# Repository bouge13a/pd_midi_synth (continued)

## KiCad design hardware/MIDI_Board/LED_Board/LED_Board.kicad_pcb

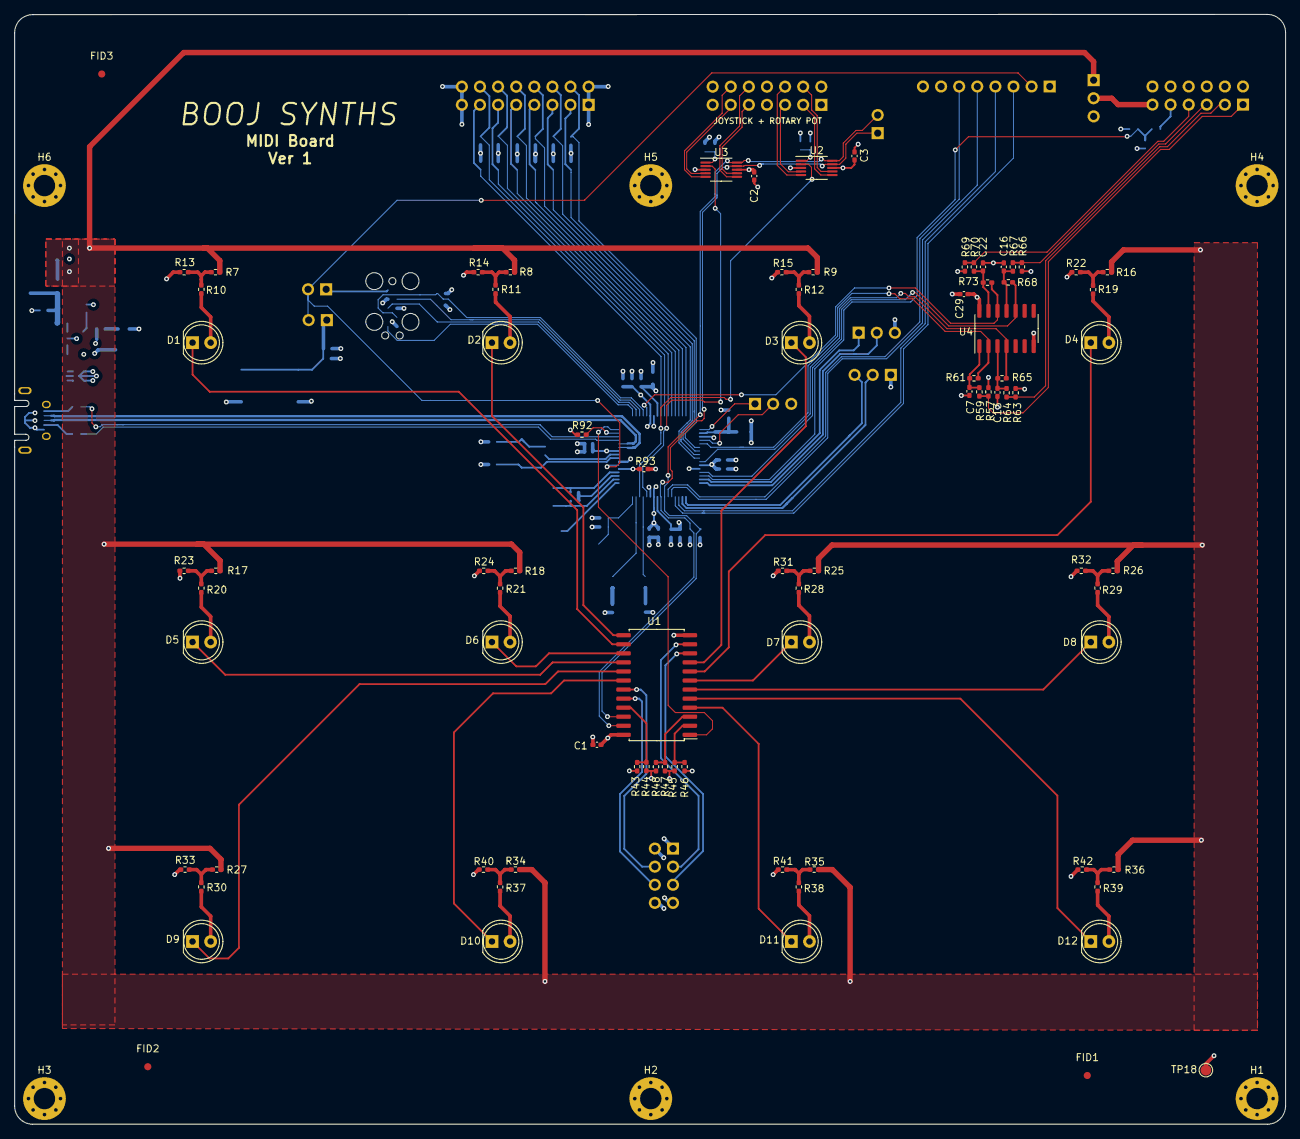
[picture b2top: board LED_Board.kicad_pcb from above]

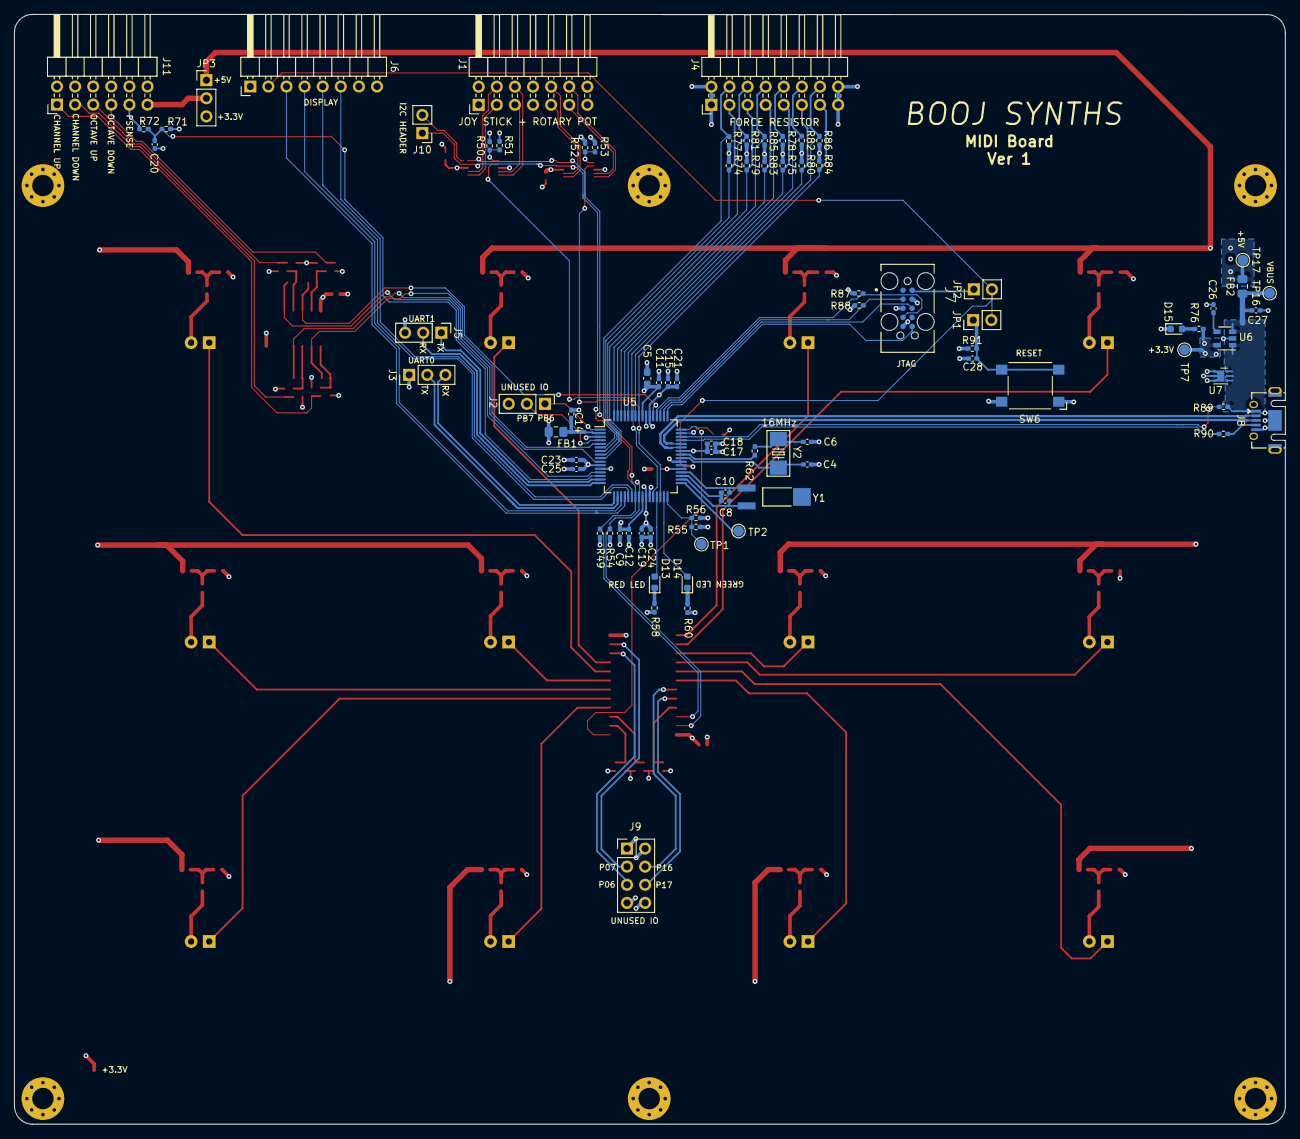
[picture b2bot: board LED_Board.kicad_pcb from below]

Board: 4 copper layers, 178.3 x 155.7 mm, 172 parts (82 on the bottom side), 129 nets.

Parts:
C1, C2, C3, C7, C11, C12, C13, C14, C16, C20, C21, C22, C23, C24, C25, C26, C28: 0.1uF; C_0402_1005Metric_Pad0.74x0.62mm_HandSolder
C4, C6: 10pF; C_0402_1005Metric_Pad0.74x0.62mm_HandSolder
C5: 2.2uF; C_0603_1608Metric_Pad1.08x0.95mm_HandSolder
C8, C10: 24pF; C_0402_1005Metric_Pad0.74x0.62mm_HandSolder
C9, C27: 1uF; C_0402_1005Metric_Pad0.74x0.62mm_HandSolder
C15, C17, C18, C19, C29: 0.01uF; C_0402_1005Metric_Pad0.74x0.62mm_HandSolder
D1, D2, D3, D4, D5, D6, D7, D8, D9, D10, D11, D12: LED; LED_D5.0mm
D13: LED_RED; LED_0603_1608Metric
D14: LED_GREEN; LED_0603_1608Metric
D15: +3.3V; LED_0603_1608Metric
FB1, FB2: 600_Ohm@100MHz; L_0805_2012Metric_Pad1.15x1.40mm_HandSolder
FID1, FID2, FID3: Fiducial_1mm_Mask3mm
H1, H2, H3, H4, H5, H6: MountingHole_Pad; MountingHole_3mm_Pad_Via
J1: Conn_02x07_Odd_Even; PinHeader_2x07_P2.54mm_Horizontal
J2, J3, J5: Conn_01x03_Male; PinHeader_1x03_P2.54mm_Vertical
J4: Conn_02x08_Odd_Even; PinHeader_2x08_P2.54mm_Horizontal
J6: Conn_01x08_Female; PinHeader_1x08_P2.54mm_Horizontal
J7: TC2050-IDC; TAG-CONNECT_TC2050-IDC
J8: USB_B_Micro; USB_Micro-AB_Molex_47590-0001
J9: Conn_02x04_Odd_Even; PinHeader_2x04_P2.54mm_Vertical
J10: Conn_01x02_Male; PinHeader_1x02_P2.54mm_Vertical
J11: Conn_02x06_Odd_Even; PinHeader_2x06_P2.54mm_Horizontal
JP1: Jumper_NC_Small; PinHeader_1x02_P2.54mm_Vertical
JP2: Jumper_NO_Small; PinHeader_1x02_P2.54mm_Vertical
JP3: Jumper_3_Open; PinHeader_1x03_P2.54mm_Vertical
R7, R8, R9, R13, R14, R15, R16, R17, R18, R22, R23, R24, R25, R26, R27, R31, R32, R33, R34, R35, R36, R40, R41, R42, R56, R61, R62, R65, R68, R73, R93: 0; R_0402_1005Metric_Pad0.72x0.64mm_HandSolder
R10, R11, R12, R19, R20, R21, R28, R29, R30, R37, R38, R39, R49, R54, R55, R57, R59, R63, R64, R66, R67, R69, R70, R71, R76, R87, R88, R91, R92: 10K; R_0402_1005Metric_Pad0.72x0.64mm_HandSolder
R43, R44, R45, R46, R47, R48, R50, R51, R52, R53, R58, R60: 4.7K; R_0402_1005Metric_Pad0.72x0.64mm_HandSolder
R72: 1K; R_0402_1005Metric_Pad0.72x0.64mm_HandSolder
R74, R75, R77, R78, R79, R80, R81, R82, R83, R84, R85, R86: 100K; R_0402_1005Metric_Pad0.72x0.64mm_HandSolder
R89, R90: 100; R_0402_1005Metric_Pad0.72x0.64mm_HandSolder
SW6: B3F-1000; SW_SPST_Omron_B3FS-100xP
TP1: WAKE_N; TestPoint_Pad_D1.5mm
TP2: HIB; TestPoint_Pad_D1.5mm
TP7: 3.3V; TestPoint_Pad_D1.5mm
TP16: VBUS; TestPoint_Pad_D1.5mm
TP17: +5V; TestPoint_Pad_D1.5mm
TP18: +3.3V; TestPoint_Pad_D1.5mm
U1: PCF8575PWR; SOIC-24W_7.5x15.4mm_P1.27mm
U2, U3: ADS1015IDGS; VSSOP-10_3x3mm_P0.5mm
U4: 74HC14; SOIC-14_3.9x8.7mm_P1.27mm
U5: TM4C123GH6PM; LQFP-64_10x10mm_P0.5mm
U6: TPS73633DBV; SOT-23-5
U7: TVS0500DRV; WSON-6-1EP_2x2mm_P0.65mm_EP1x1.6mm
Y1: 32.768KHz; XTAL_AB26TRB-32.768KHZ-T
Y2: 16MHz; CRYSTAL_5_3.2MM

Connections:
+3.3VA: C14.1, FB1.2, U5.2
+3V3: C1.1, C2.1, C3.1, C15.1, C17.1, C18.1, C19.1, C21.1, C23.1, C24.1, C25.1, C29.1, FB1.1, J1.1, J1.2, J4.1, J4.2, J4.15, J4.16, J6.7, JP3.3, R13.1, R14.1, R15.1, R22.1, R23.1, R24.1, R31.1, R32.1, R33.1, R40.1, R41.1, R42.1, R43.1, R45.1, R47.1, R49.1, R50.1, R52.1, R54.1, R55.1, R57.1, R63.1, R66.1, R69.1, R71.1, R76.1, R87.1, R88.1, R91.1, R93.2, TP7.1, TP18.1, U1.24, U2.8, U3.8, U4.14, U5.11, U5.26, U5.42, U5.54, U6.5
+5V: FB2.1, JP3.1, R7.1, R8.1, R9.1, R16.1, R17.1, R18.1, R25.1, R26.1, R27.1, R34.1, R35.1, R36.1, TP17.1
/MCU USB POWER IO/GNDX: C8.2, C10.1, U5.35
/MCU USB POWER IO/GREEN_LED: D14.2, U5.31
/MCU USB POWER IO/OSC0: C4.1, U5.40, Y2.1
/MCU USB POWER IO/OSC1: C6.1, R62.2, Y2.2
/MCU USB POWER IO/RED_LED: D13.2, U5.29
/MCU USB POWER IO/WAKE_N: R55.2, R56.1, TP1.1, U5.32
/MCU USB POWER IO/XOSC0: C8.1, U5.34, Y1.1
/MCU USB POWER IO/XOSC1: C10.2, U5.36, Y1.2
ADC0_IN0: J1.11, U3.4
ADC0_IN1: J1.12, U3.5
ADC0_IN2: J1.10, U3.6
ADC0_IN3: J1.9, U3.7
ADC0_RDY: U3.2, U5.28
ADC1_IN0: J1.5, U2.4
ADC1_IN1: J1.6, U2.5
ADC1_IN2: J1.3, U2.6
ADC1_IN3: J1.4, U2.7
ADC1_RDY: U2.2, U5.30
AIN0: J4.4, R77.1, U5.6
AIN1: J4.3, R74.1, U5.7
AIN2: J4.6, R81.1, U5.8
AIN3: J4.5, R79.1, U5.9
AIN4: J4.8, R85.1, U5.64
AIN5: J4.7, R83.1, U5.63
AIN6: J4.10, R78.1, U5.62
AIN7: J4.9, R75.1, U5.61
AIN8: J4.12, R82.1, U5.60
AIN9: J4.11, R80.1, U5.59
AIN10: J4.14, R86.1, U5.58
AIN11: J4.13, R84.1, U5.57
BOARD_ID: R92.1, U5.47
CHN_DWN: R65.1, U4.4, U5.10
CHN_UP: R61.1, U4.2, U5.5
DISP_CLK: J6.4, U5.19
DISP_MISO: J6.5, U5.21
DISP_MOSI: J6.6, U5.22
DISP_SS: J6.3, U5.20
GND: C1.2, C2.2, C3.2, C4.2, C5.2, C6.2, C7.2, C9.2, C11.2, C12.2, C13.2, C14.2, C15.2, C16.2, C17.2, C18.2, C19.2, C20.2, C21.2, C22.2, C23.2, C24.2, C25.2, C26.2, C27.2, C28.2, C29.2, D15.1, H1.1, H2.1, H3.1, H4.1, H5.1, H6.1, J1.7, J1.8, J1.13, J1.14, J2.3, J3.1, J5.3, J6.8, J7.3, J7.5, J7.9, J8.5, J8.6, J9.1, J9.2, J9.7, J9.8, J11.2, J11.4, J11.6, J11.8, J11.10, J11.12, R44.2, R46.2, R48.2, R51.2, R53.2, R56.2, R58.2, R60.2, R74.2, R75.2, R77.2, R78.2, R79.2, R80.2, R81.2, R82.2, R83.2, R84.2, R85.2, R86.2, R92.2, SW6.1, SW6.2, U1.12, U2.3, U3.3, U4.7, U5.3, U5.12, U5.27, U5.39, U5.55, U6.2, U7.1, U7.2, U7.3, U7.7
I2C_SCL: J10.2, R49.2, U1.22, U2.10, U3.10, U5.23
I2C_SDA: J10.1, R54.2, U1.23, U2.9, U3.9, U5.24
IOE_A0: R43.2, R44.1, U1.21
IOE_A1: R45.2, R46.1, U1.2
IOE_A2: R47.2, R48.1, U1.3
IO_EXP_INT_N: U1.1, U5.48
JTAG_RST_N: J7.10, JP2.1
JTAG_TCK: J7.4, R87.2, U5.52
JTAG_TDI: J7.8, U5.50
JTAG_TDO: J7.6, U5.49
JTAG_TMS: J7.2, R88.2, U5.51
LED0: D10.1, U1.18
LED1: D9.1, U1.17
LED2: D5.1, U1.16
LED3: D6.1, U1.15
LED4: D1.1, U1.14
LED5: D2.1, U1.13
LED6: D3.1, U1.9
LED7: D4.1, U1.8
LED8: D7.1, U1.7
LED9: D8.1, U1.6
LED10: D12.1, U1.5
LED11: D11.1, U1.4
unnamed: C7.1, R59.2, R61.2, U4.1
unnamed: C13.1, R64.2, R65.2, U4.3
unnamed: C16.1, R67.2, R68.2, U4.11
unnamed: C22.1, R70.2, R73.2, U4.13
unnamed: C26.1, U6.4
unnamed: C28.1, JP1.1, R91.2, SW6.3, SW6.4
unnamed: D1.2, R10.2
unnamed: D2.2, R11.2
unnamed: D3.2, R12.2
unnamed: D4.2, R19.2
unnamed: D5.2, R20.2
unnamed: D6.2, R21.2
unnamed: D7.2, R28.2
unnamed: D8.2, R29.2
unnamed: D9.2, R30.2
unnamed: D10.2, R37.2
unnamed: D11.2, R38.2
unnamed: D12.2, R39.2
unnamed: D13.1, R58.1
unnamed: D14.1, R60.1
unnamed: D15.2, R76.2
unnamed: J8.4, R90.1
unnamed: J11.11, JP3.2
unnamed: R7.2, R10.1, R13.2
unnamed: R8.2, R11.1, R14.2
unnamed: R9.2, R12.1, R15.2
unnamed: R16.2, R19.1, R22.2
unnamed: R17.2, R20.1, R23.2
unnamed: R18.2, R21.1, R24.2
unnamed: R25.2, R28.1, R31.2
unnamed: R26.2, R29.1, R32.2
unnamed: R27.2, R30.1, R33.2
unnamed: R34.2, R37.1, R40.2
unnamed: R35.2, R38.1, R41.2
unnamed: R36.2, R39.1, R42.2
unnamed: R50.2, R51.1, U2.1
unnamed: R52.2, R53.1, U3.1
unnamed: R62.1, U5.41
unnamed: R93.1, U5.37
unnamed: TP2.1, U5.33
OCT_DWN: R73.1, U4.12, U5.53
OCT_UP: R68.1, U4.10, U5.13
P06: J9.5, U1.10
P07: J9.3, U1.11
P16: J9.4, U1.19
P17: J9.6, U1.20
PB6: J2.1, U5.1
PB7: J2.2, U5.4
P_SENSE: C20.1, R71.2, R72.2, U5.14
RST_N: J6.2, JP1.2, JP2.2, U5.38
SW_CHN_DWN: J11.3, R63.2, R64.1
SW_CHN_UP: J11.1, R57.2, R59.1
SW_OCT_DWN: J11.7, R69.2, R70.1
SW_OCT_UP: J11.5, R66.2, R67.1
SW_PSENSE: J11.9, R72.1
UART0_RX: J3.3, U5.17
UART0_TX: J3.2, U5.18
UART1_RX: J5.2, U5.16
UART1_TX: J5.1, U5.15
USB_D+: J8.3, U5.44
USB_D-: J8.2, U5.43
USB_ID: R90.2, U5.45
USB_VBUS: R89.2, U5.46
VBUS: C27.1, FB2.2, J8.1, R89.1, TP16.1, U6.1, U6.3, U7.4, U7.5, U7.6
VDDC: C5.1, C9.1, C11.1, C12.1, U5.25, U5.56

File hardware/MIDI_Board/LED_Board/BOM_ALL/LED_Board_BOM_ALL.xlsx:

Comment | Designator | Footprint | LCSC | Other Vendors
0.01uF | C15,C17,C18,C19,C29 | Capacitor_SMD:C_0402_1005Metric_Pad0.74x0.62mm_HandSolder | C15195
0.1uF | C1,C2,C3,C7,C11,C12,C13,C14,C16,C20,C21,C22,C23,C24,C25,C26,C28 | Capacitor_SMD:C_0402_1005Metric_Pad0.74x0.62mm_HandSolder | C1525
10pF | C4,C6 | Capacitor_SMD:C_0402_1005Metric_Pad0.74x0.62mm_HandSolder | C32949
2.2uF | C5 | Capacitor_SMD:C_0603_1608Metric_Pad1.08x0.95mm_HandSolder | C57895
24pF | C8,C10 | Capacitor_SMD:C_0402_1005Metric_Pad0.74x0.62mm_HandSolder | C22728
1uF | C9,C27 | Capacitor_SMD:C_0402_1005Metric_Pad0.74x0.62mm_HandSolder | C28323
LED | D1,D2,D3,D4,D5,D6,D7,D8,D9,D10,D11,D12 | LED_THT:LED_D5.0mm
LED_RED | D13 | LED_SMD:LED_0603_1608Metric | C72044
LED_GREEN | D14 | LED_SMD:LED_0603_1608Metric | C72043
+3.3V | D15 | LED_SMD:LED_0603_1608Metric | C72043
600_Ohm@100MHz | FB1,FB2 | Inductor_SMD:L_0805_2012Metric_Pad1.15x1.40mm_HandSolder | C1017
Conn_02x07_Odd_Even | J1 | Connector_PinHeader_2.54mm:PinHeader_2x07_P2.54mm_Horizontal |  | HTSS-114-04-G-D-RA
Conn_01x02_Male | J10 | Connector_PinHeader_2.54mm:PinHeader_1x02_P2.54mm_Vertical | C160332
Conn_02x06_Odd_Even | J11 | Connector_PinHeader_2.54mm:PinHeader_2x06_P2.54mm_Horizontal |  | HTSS-106-04-G-D-RA
Conn_01x03_Male | J2,J3,J5 | Connector_PinHeader_2.54mm:PinHeader_1x03_P2.54mm_Vertical | C306138
Conn_02x08_Odd_Even | J4 | Connector_PinHeader_2.54mm:PinHeader_2x08_P2.54mm_Horizontal |  | HTSS-116-04-G-D-RA
Conn_01x08_Female | J6 | Connector_PinHeader_2.54mm:PinHeader_1x08_P2.54mm_Horizontal |  | 640457-8 | TE connectivity
TC2050-IDC | J7 | TC2050-IDC:TAG-CONNECT_TC2050-IDC
USB_B_Micro | J8 | Connector_USB:USB_Micro-AB_Molex_47590-0001 | C145779
Conn_02x04_Odd_Even | J9 | Connector_PinHeader_2.54mm:PinHeader_2x04_P2.54mm_Vertical |  | TSW-104-23-G-D
Jumper_NC_Small | JP1 | Connector_PinHeader_2.54mm:PinHeader_1x02_P2.54mm_Vertical | C160332
Jumper_NO_Small | JP2 | Connector_PinHeader_2.54mm:PinHeader_1x02_P2.54mm_Vertical | C160332
Jumper_3_Open | JP3 | Connector_PinHeader_2.54mm:PinHeader_1x03_P2.54mm_Vertical | C306138
4.7K | R43,R44,R45,R46,R47,R48,R50,R51,R52,R53,R58,R60 | Resistor_SMD:R_0402_1005Metric_Pad0.72x0.64mm_HandSolder | C25900
10K | R10,R11,R12,R19,R20,R21,R28,R29,R30,R37,R38,R39,R49,R54,R55,R57,R59,R63,R64,R66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 | Resistor_SMD:R_0402_1005Metric_Pad0.72x0.64mm_HandSolder | C25744
0 | R7,R8,R9,R13,R14,R15,R16,R17,R18,R22,R23,R24,R25,R26,R27,R31,R32,R33,R34,R35,R3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 | Resistor_SMD:R_0402_1005Metric_Pad0.72x0.64mm_HandSolder | C17168
1K | R72 | Resistor_SMD:R_0402_1005Metric_Pad0.72x0.64mm_HandSolder | C11702
100K | R74,R75,R77,R78,R79,R80,R81,R82,R83,R84,R85,R86 | Resistor_SMD:R_0402_1005Metric_Pad0.72x0.64mm_HandSolder | C25741
100 | R89,R90 | Resistor_SMD:R_0402_1005Metric_Pad0.72x0.64mm_HandSolder | C25076
B3F-1000 | SW6 | Button_Switch_SMD:SW_SPST_Omron_B3FS-100xP | C271750
PCF8575PWR | U1 | Package_SO:SOIC-24W_7.5x15.4mm_P1.27mm | C694757
ADS1015IDGS | U2,U3 | Package_SO:TSSOP-10_3x3mm_P0.5mm | C193969
74HC14 | U4 | Package_SO:SOIC-14_3.9x8.7mm_P1.27mm | C130461
TM4C123GH6PM | U5 | Package_QFP:LQFP-64_10x10mm_P0.5mm | C544750
TPS73633DBV | U6 | Package_TO_SOT_SMD:SOT-23-5 | C28038
TVS0500DRV | U7 | Package_SON:WSON-6-1EP_2x2mm_P0.65mm_EP1x1.6mm |  | TVS0500DRVR
32.768KHz | Y1 | AB26TRB-32:XTAL_AB26TRB-32.768KHZ-T |  | AB26TRB-32.768KHZ-T
16MHz | Y2 | NX5032GA-16MHZ:CRYSTAL_5_3.2MM |  | NX5032GA-16MHZ-STD-CSK-4

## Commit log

2021-04-01 First commit, starting point for new projects
2021-04-01 Added rpi uart task
2021-04-02 added host uart, needs testing
2021-04-02 Added ADC pins
2021-04-02 added event groups, problem with two adc interrupts
2021-04-02 ADCs are working
2021-04-02 Started using ADC module 1
2021-04-03 WIP comparators, fault isr hitting
2021-04-03 fixed comp init issue
2021-04-04 Added non pressure sensitive keys, needs testing and tab
2021-04-04 added write to page feature, needs testing
2021-04-04 added ability to write to page, last commit depricated
2021-04-05 made a bunch of fixes, serial terminal broken
2021-04-05 adc works, but adding comparators breaks it
2021-04-05 removed comp ints
2021-04-06 added new adc drumpad system, made messages print to screen
2021-04-06 fixed state machine, needs pressure sense
2021-04-07 pressure sense works in terminal, needs debounce state
2021-04-07 added slope, still has bugs
2021-04-08 Pressure sense works decently, need knobs and equation
2021-04-09 moved sequence data get to interrupt
2021-04-09 works teensy, needs i2c stuff
2021-04-10 WIP added rotary encoder, needs spi
2021-04-10 Added rotary encoder with 7 seg dusplay
2021-04-10 fixed rotary encoder
2021-04-10 WIP added joystick task
2021-04-10 Adc is non deterministic need to remove event group
2021-04-10 removed event groups
2021-04-11 fixed i2c error
2021-04-11 separated firmware into two boards
2021-04-11 fixed i2c driver
2021-04-12 fixed i2c task to reverse receive order
2021-04-14 added volume and sensitivity
2021-04-14 fixed naive joystick function to send stop msg
2021-04-14 fixed i2c problem, ADC was too slow
2021-04-14 added midi knobs feature
2021-04-15 added midi buttons task and volume needs psense testing
2021-04-15 fixed some shit
2021-04-17 Added USB HID looper pins and started looper buttons tak
2021-04-17 Added looper buttons messages, changed gpis to wpd
2021-04-18 fixed usb problem, stack size too small
2021-04-20 fixed looper buttons
2021-04-20 added effects and volumes
2021-04-22 got teensy working with midi controller
2021-04-22 added 10 sound levels to touch pad
2021-04-22 added knob uart messages
2021-04-24 fixed joystick
2021-04-24 fixed joystick for real this time
2021-04-25 added channel pressure
2021-05-03 made debug changes to looper
2021-05-04 added channel select
2021-05-04 fixed midi channel select
2021-05-04 added send data functions for init
2021-05-18 ready to add usb midi
2021-06-09 not really sure
2021-07-27 new stuff
2022-02-10 fixed linking problems
2022-02-10 added hardware
